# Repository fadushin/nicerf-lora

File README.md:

This repository contains [KiCad5](https://www.kicad.org) files for a small (less than 1" square) 2-sided PCB that can be used to integrate a [NiceRF SX127X](https://www.nicerf.com/products/detail/100mw-lora-wireless-transceiver-module-lora1276-915.html) (or equivalent) LoRa transceiver into your maker projects.

The [NiceRF SX127X](https://www.nicerf.com/products/detail/100mw-lora-wireless-transceiver-module-lora1276-915.html) LoRa transceiver has some desirable properties, such as its small form factor, ability to integrate flexibly with ESP32 projects (unlike some integrated development boards), and it is probably one of the more affordable SX127X boards out there.  In addition, the NiceRF team provides great support for their products.

This PCB adds support for:

* One [NiceRF SX127X](https://www.nicerf.com/products/detail/100mw-lora-wireless-transceiver-module-lora1276-915.html) module
* 2.54mm pins for GND, +3.3v, MOSI, MISO, SCLK, NSS, RESET (optional), and DPIO_0 pins on the NiceRF board, making the board slightly easier to use with standard dupont wires or breadboards;
* A set of pads for a standard IPEX antenna connector;
* A 1206 SMT 10k ohm resistor for the RESET circuit;
* Two 1206 SMT capacitors (optional).

Caveats:

* Currently no support for `DIO_1` and `DIO_2` pins (but could be added easily);
* Only tested on SX1276-915 modules;
* Has not been tested with SWT or VNA meter for antenna circuit leakage or reflection.

This work is licensed under the terms of the BSD License 2.0.  Enjoy!

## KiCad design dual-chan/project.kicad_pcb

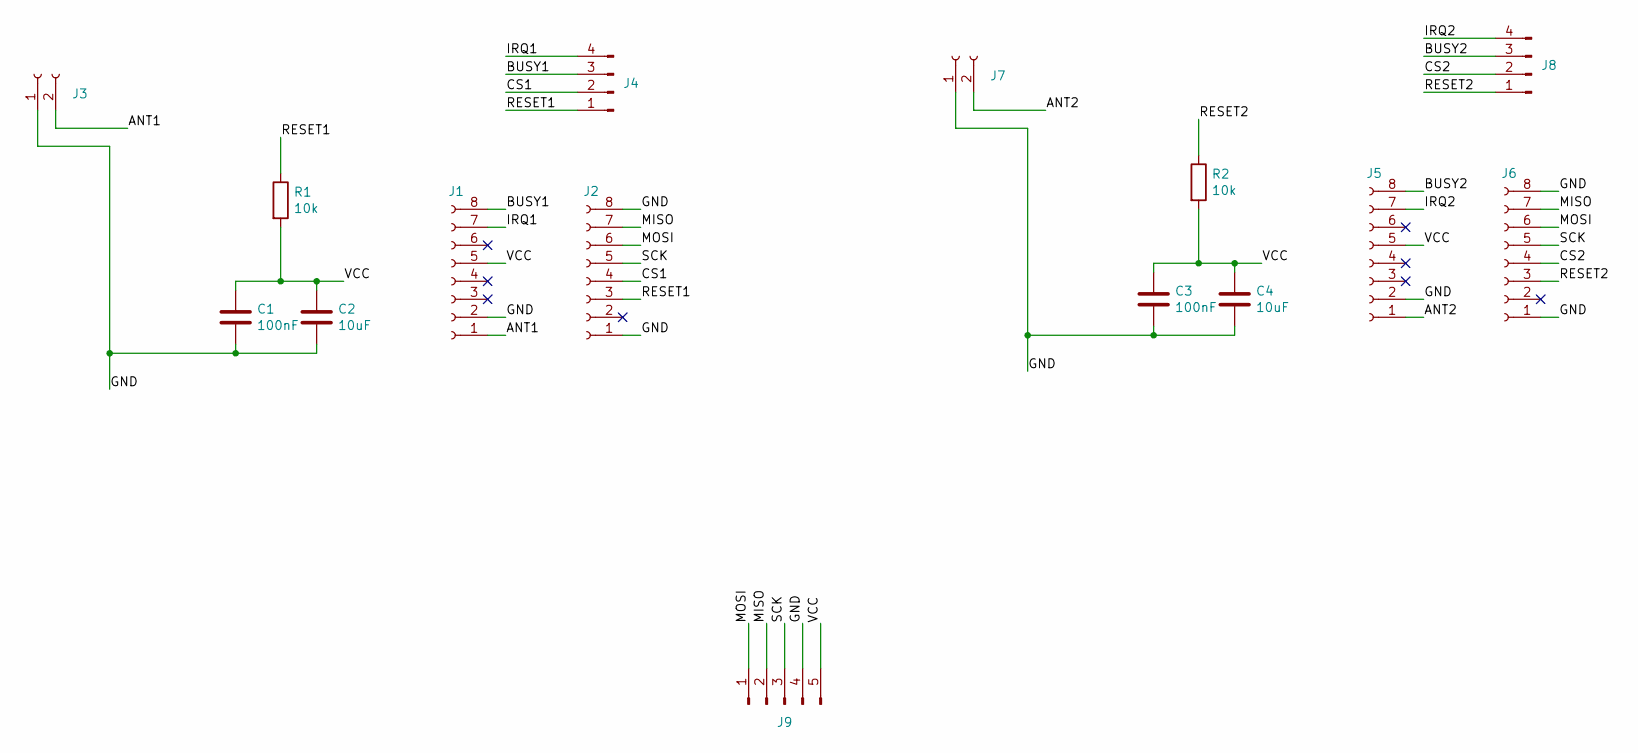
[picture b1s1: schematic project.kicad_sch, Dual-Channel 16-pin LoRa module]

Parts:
C1, C3: 100nF; C_1206_3216Metric_Pad1.33x1.80mm_HandSolder
C2, C4: 10uF; C_1206_3216Metric_Pad1.33x1.80mm_HandSolder
J1, J2, J5, J6: Conn_01x08_Female; PinSocket_1x08_P2.00mm_Vertical
J3, J7: Conn_01x02_Female; IPEX_Antenna_Connector
J4, J8: Conn_01x04_Male; PinHeader_1x04_P2.54mm_Vertical
J9: Conn_01x05_Male; PinHeader_1x05_P2.54mm_Vertical
R1, R2: 10k; R_1206_3216Metric_Pad1.30x1.75mm_HandSolder

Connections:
/ANT1: J1.1, J3.2
/ANT2: J5.1, J7.2
/BUSY1: J1.8, J4.3
/BUSY2: J5.8, J8.3
/CS1: J2.4, J4.2
/CS2: J6.4, J8.2
/GND: C1.2, C2.2, C3.2, C4.2, J1.2, J2.1, J2.8, J3.1, J5.2, J6.1, J6.8, J7.1, J9.4
/IRQ1: J1.7, J4.4
/IRQ2: J5.7, J8.4
/MISO: J2.7, J6.7, J9.2
/MOSI: J2.6, J6.6, J9.1
/RESET1: J2.3, J4.1, R1.1
/RESET2: J6.3, J8.1, R2.1
/SCK: J2.5, J6.5, J9.3
/VCC: C1.1, C2.1, C3.1, C4.1, J1.5, J5.5, J9.5, R1.2, R2.2

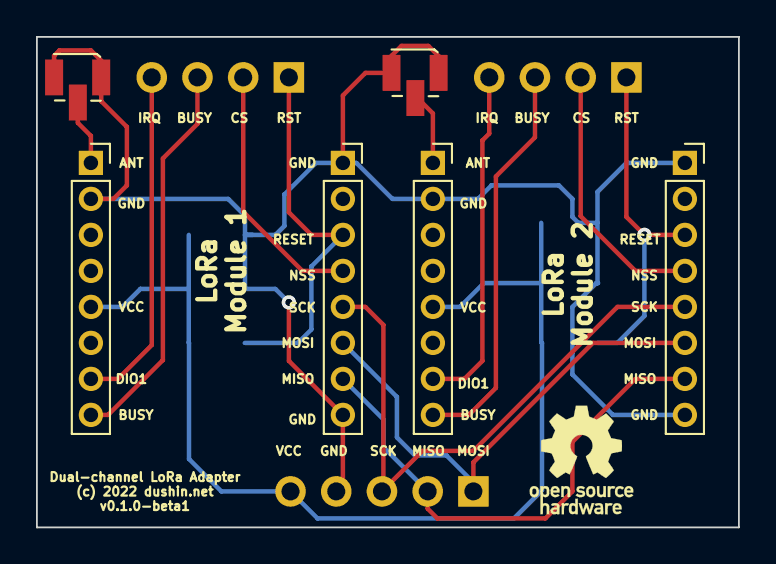
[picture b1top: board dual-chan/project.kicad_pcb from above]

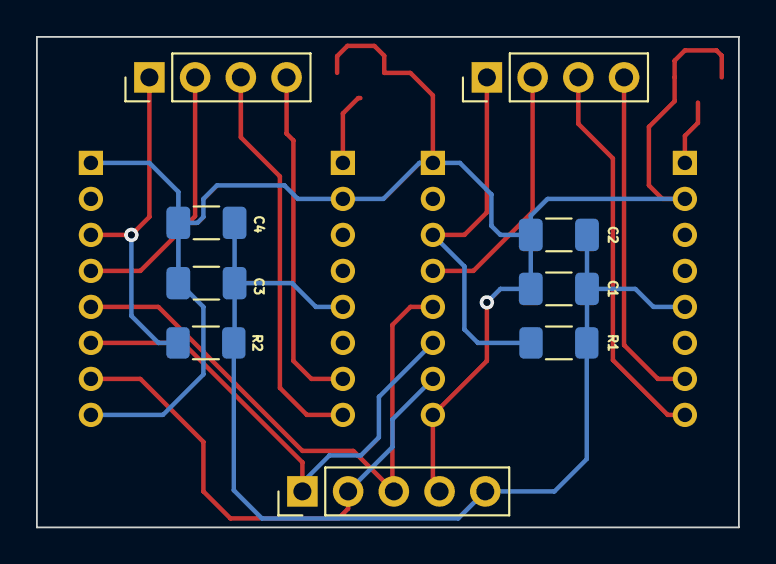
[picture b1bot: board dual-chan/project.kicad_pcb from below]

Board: 2 copper layers, 39.0 x 27.2 mm, 15 parts (9 on the bottom side), 15 nets.

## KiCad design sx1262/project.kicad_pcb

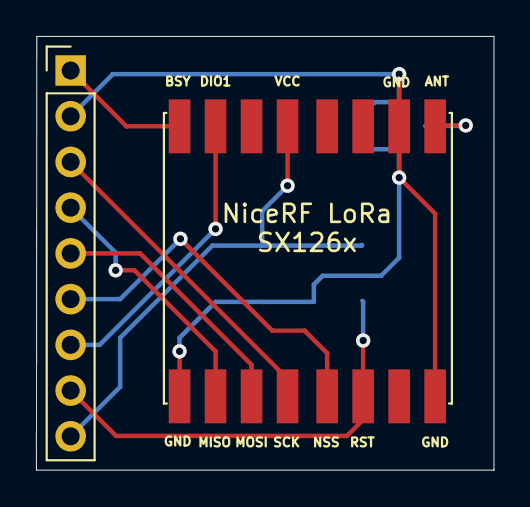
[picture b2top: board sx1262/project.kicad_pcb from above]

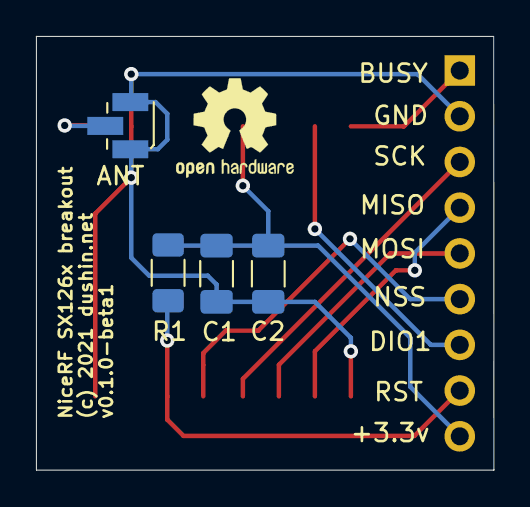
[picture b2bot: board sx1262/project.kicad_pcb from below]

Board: 2 copper layers, 25.4 x 24.1 mm, 6 parts (4 on the bottom side), 10 nets.

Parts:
C1: 100nF; C_1206_3216Metric_Pad1.33x1.80mm_HandSolder
C2: 10uF; C_1206_3216Metric_Pad1.33x1.80mm_HandSolder
J1: Conn_01x09_Female; PinHeader_1x09_P2.54mm_Vertical
J2: Conn_01x02_Female; IPEX_Antenna_Connector
R1: 10k; R_1206_3216Metric_Pad1.30x1.75mm_HandSolder
U1: nicerf-lora-sx1262

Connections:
/ANT: J2.2, U1.9
/BUSY: J1.1, U1.16
/DIO0: J1.7, U1.15
/GND: C1.2, C2.2, J1.2, J2.1, U1.1, U1.8, U1.10
/MISO: J1.4, U1.2
/MOSI: J1.5, U1.3
/NSS: J1.6, U1.5
/RESET: J1.8, R1.1, U1.6
/SCK: J1.3, U1.4
/VCC: C1.1, C2.1, J1.9, R1.2, U1.13

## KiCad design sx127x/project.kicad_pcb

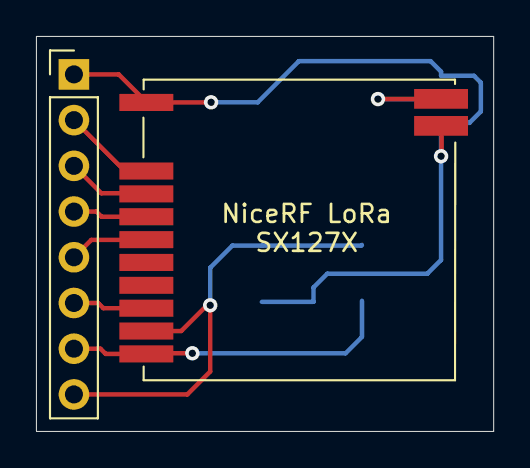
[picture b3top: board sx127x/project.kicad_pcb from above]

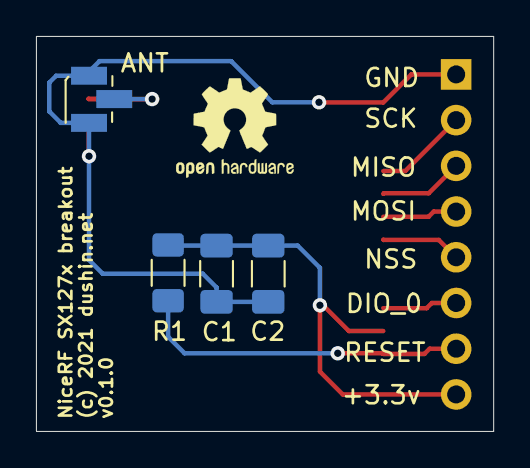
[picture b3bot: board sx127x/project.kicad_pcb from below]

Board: 2 copper layers, 25.4 x 21.9 mm, 6 parts (4 on the bottom side), 9 nets.

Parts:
C1: 100pF; C_1206_3216Metric_Pad1.33x1.80mm_HandSolder
C2: 102pF; C_1206_3216Metric_Pad1.33x1.80mm_HandSolder
J1: Conn_01x08_Female; PinHeader_1x08_P2.54mm_Vertical
J2: Conn_01x02_Female; IPEX_Antenna_Connector
R1: 10k; R_1206_3216Metric_Pad1.30x1.75mm_HandSolder
U1: NiceRF SX127X; nicerf-lora-sx127x

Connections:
/ANT: J2.2, U1.13
/DIO0: J1.6, U1.10
/GND: C1.2, C2.2, J1.1, J2.1, U1.1, U1.14
/MISO: J1.3, U1.5
/MOSI: J1.4, U1.6
/NSS: J1.5, U1.7
/RESET: J1.7, R1.1, U1.12
/SCK: J1.2, U1.4
/VCC: C1.1, C2.1, J1.8, R1.2, U1.11

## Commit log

2021-08-29 NiceRF SX127X breakout board
2022-01-10 Moved sx127x files into its own directory.
2022-01-10 Added Kicad files for SX1262
2022-03-19 Added dual-channel RF adapter

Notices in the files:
dual-chan/project.kicad_pcb:
(c) 2022 dushin.net
sx1262/project.kicad_pcb:
(c) 2021 dushin.net
